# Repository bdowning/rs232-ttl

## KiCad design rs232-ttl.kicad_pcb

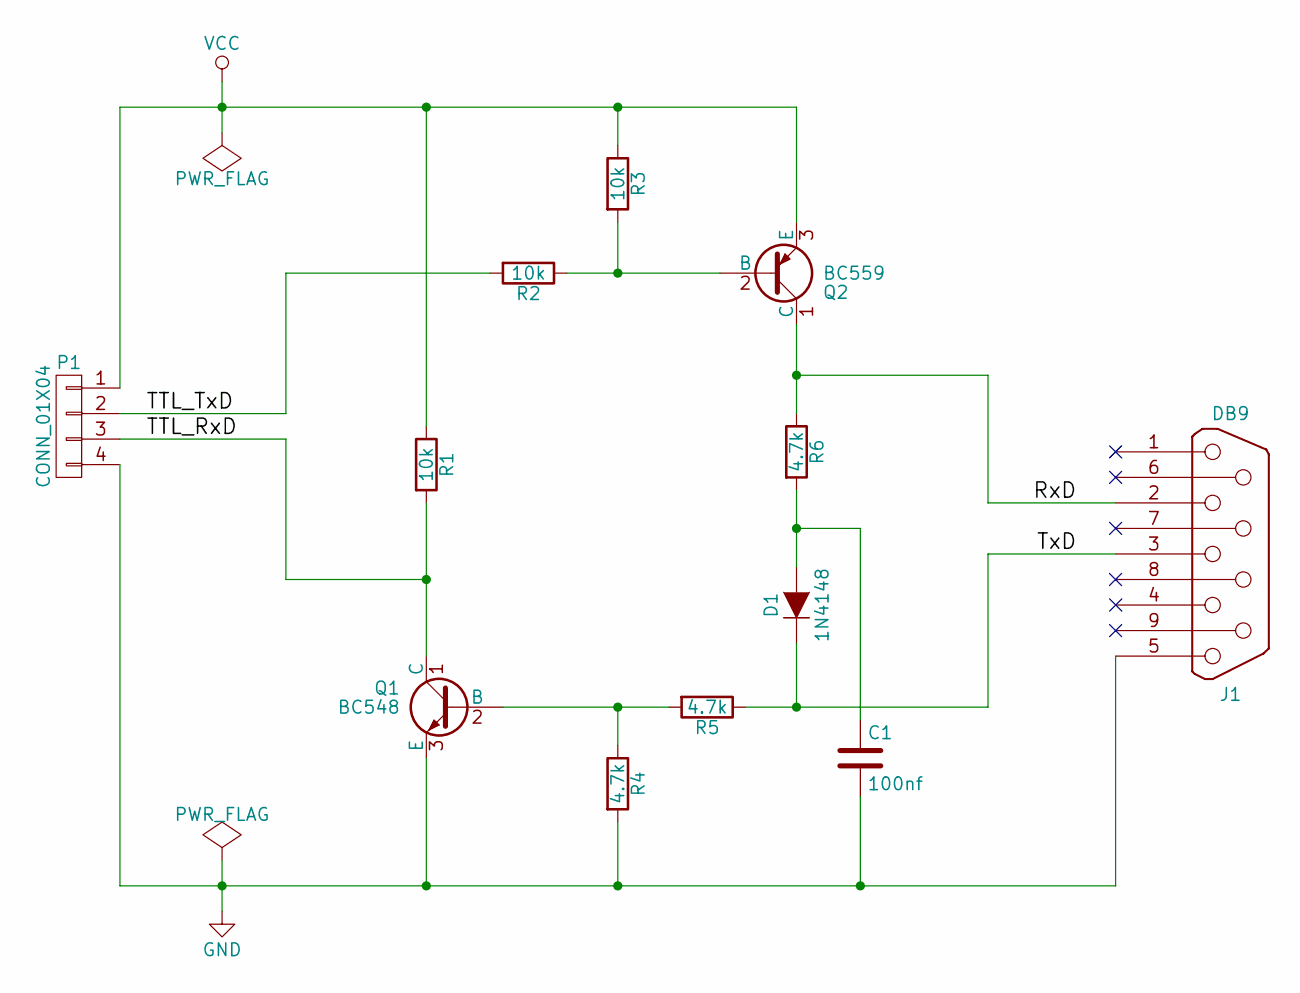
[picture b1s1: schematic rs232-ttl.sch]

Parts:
C1: 100nf; C_Disc_D6_P5
D1: 1N4148; Diode_DO-41_SOD81_Horizontal_RM10
J1: DB9; DB9FC
P1: CONN_01X04; Pin_Header_Straight_1x04
Q1: BC548; TO-92_Inline_Wide
Q2: BC559; TO-92_Inline_Wide
R1, R2, R3: 10k; Resistor_Horizontal_RM10mm
R4, R5, R6: 4.7k; Resistor_Horizontal_RM10mm

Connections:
/RxD: J1.2, Q2.1 (C), R6.1
/TTL_RxD: P1.3, Q1.1 (C), R1.2
/TTL_TxD: P1.2, R2.2
/TxD: D1.1 (K), J1.3, R5.1
GND: C1.2, J1.5, P1.4, Q1.3 (E), R4.2
unnamed: C1.1, D1.2 (A), R6.2
unnamed: Q1.2 (B), R4.1, R5.2
unnamed: Q2.2 (B), R2.1, R3.2
VCC: P1.1, Q2.3 (E), R1.1, R3.1

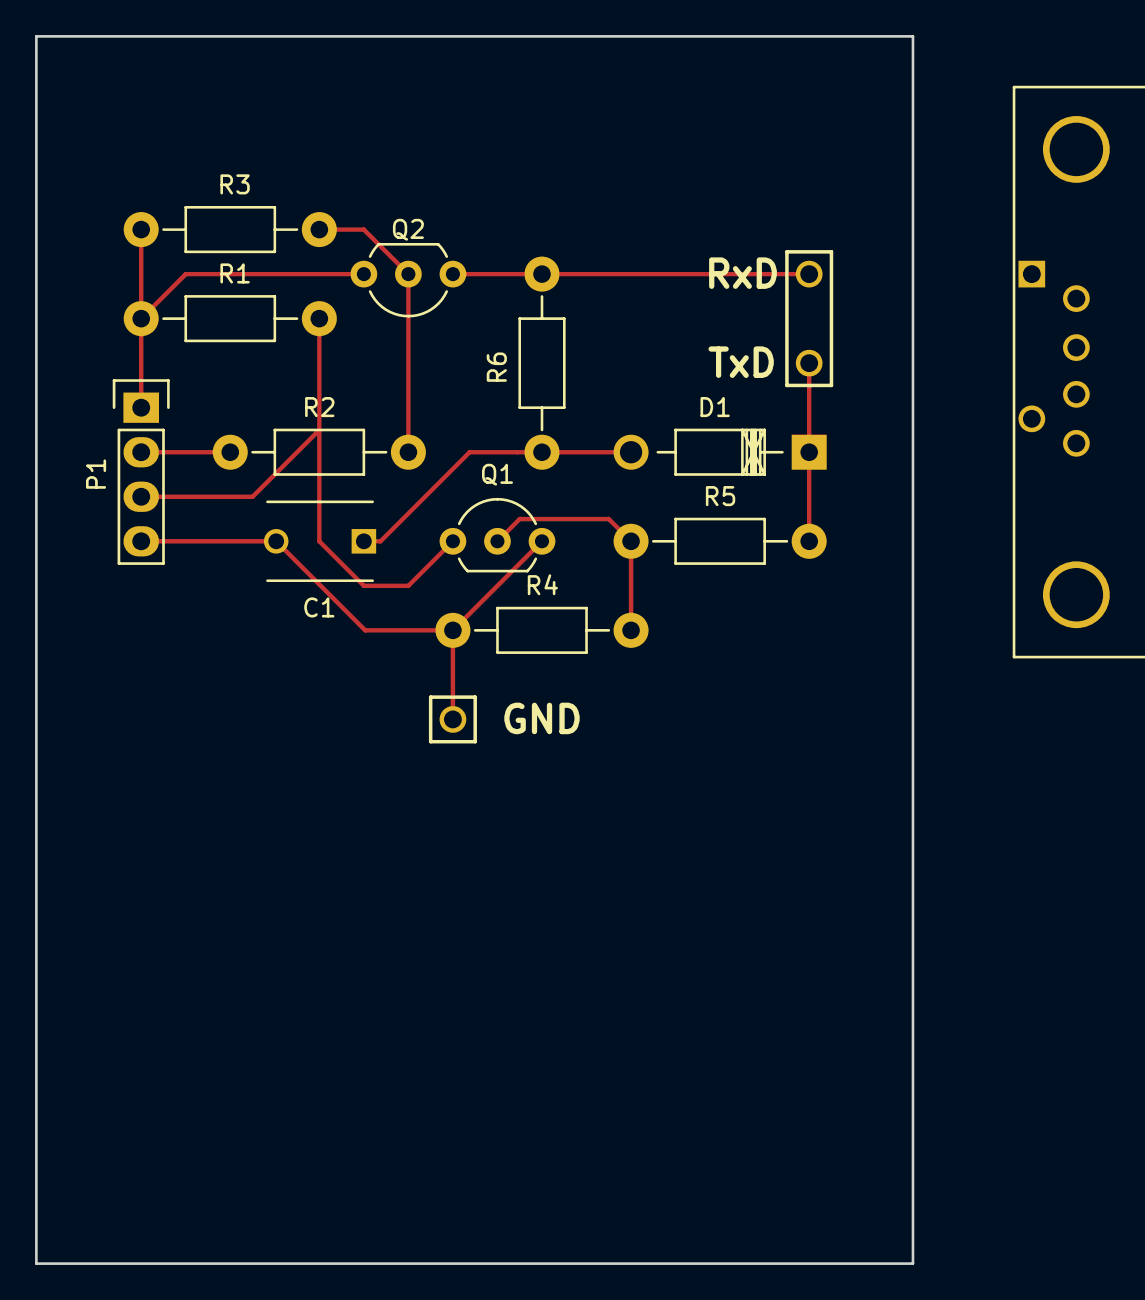
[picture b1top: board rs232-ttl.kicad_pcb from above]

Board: 4 copper layers, 50.0 x 70.0 mm, 12 parts (0 on the bottom side), 9 nets.

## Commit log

2016-05-03 RS232-TTL converter board
